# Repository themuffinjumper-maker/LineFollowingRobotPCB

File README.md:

# lfr_pcb

## Getting started

To make it easy for you to get started with GitLab, here's a list of recommended next steps.

Already a pro? Just edit this README.md and make it your own. Want to make it easy? [Use the template at the bottom](#editing-this-readme)!

## Add your files

- [ ] [Create](https://docs.gitlab.com/ee/user/project/repository/web_editor.html#create-a-file) or [upload](https://docs.gitlab.com/ee/user/project/repository/web_editor.html#upload-a-file) files
- [ ] [Add files using the command line](https://docs.gitlab.com/topics/git/add_files/#add-files-to-a-git-repository) or push an existing Git repository with the following command:

```
cd existing_repo
git remote add origin https://eng-git.canterbury.ac.nz/ogl15/lfr_pcb.git
git branch -M main
git push -uf origin main
```

## Integrate with your tools

- [ ] [Set up project integrations](https://eng-git.canterbury.ac.nz/ogl15/lfr_pcb/-/settings/integrations)

## Collaborate with your team

- [ ] [Invite team members and collaborators](https://docs.gitlab.com/ee/user/project/members/)
- [ ] [Create a new merge request](https://docs.gitlab.com/ee/user/project/merge_requests/creating_merge_requests.html)
- [ ] [Automatically close issues from merge requests](https://docs.gitlab.com/ee/user/project/issues/managing_issues.html#closing-issues-automatically)
- [ ] [Enable merge request approvals](https://docs.gitlab.com/ee/user/project/merge_requests/approvals/)
- [ ] [Set auto-merge](https://docs.gitlab.com/user/project/merge_requests/auto_merge/)

## Test and Deploy

Use the built-in continuous integration in GitLab.

- [ ] [Get started with GitLab CI/CD](https://docs.gitlab.com/ee/ci/quick_start/)
- [ ] [Analyze your code for known vulnerabilities with Static Application Security Testing (SAST)](https://docs.gitlab.com/ee/user/application_security/sast/)
- [ ] [Deploy to Kubernetes, Amazon EC2, or Amazon ECS using Auto Deploy](https://docs.gitlab.com/ee/topics/autodevops/requirements.html)
- [ ] [Use pull-based deployments for improved Kubernetes management](https://docs.gitlab.com/ee/user/clusters/agent/)
- [ ] [Set up protected environments](https://docs.gitlab.com/ee/ci/environments/protected_environments.html)

***

# Editing this README

When you're ready to make this README your own, just edit this file and use the handy template below (or feel free to structure it however you want - this is just a starting point!). Thanks to [makeareadme.com](https://www.makeareadme.com/) for this template.

## Suggestions for a good README

Every project is different, so consider which of these sections apply to yours. The sections used in the template are suggestions for most open source projects. Also keep in mind that while a README can be too long and detailed, too long is better than too short. If you think your README is too long, consider utilizing another form of documentation rather than cutting out information.

## Name
Choose a self-explaining name for your project.

## Description
Let people know what your project can do specifically. Provide context and add a link to any reference visitors might be unfamiliar with. A list of Features or a Background subsection can also be added here. If there are alternatives to your project, this is a good place to list differentiating factors.

## Badges
On some READMEs, you may see small images that convey metadata, such as whether or not all the tests are passing for the project. You can use Shields to add some to your README. Many services also have instructions for adding a badge.

## Visuals
Depending on what you are making, it can be a good idea to include screenshots or even a video (you'll frequently see GIFs rather than actual videos). Tools like ttygif can help, but check out Asciinema for a more sophisticated method.

## Installation
Within a particular ecosystem, there may be a common way of installing things, such as using Yarn, NuGet, or Homebrew. However, consider the possibility that whoever is reading your README is a novice and would like more guidance. Listing specific steps helps remove ambiguity and gets people to using your project as quickly as possible. If it only runs in a specific context like a particular programming language version or operating system or has dependencies that have to be installed manually, also add a Requirements subsection.

## Usage
Use examples liberally, and show the expected output if you can. It's helpful to have inline the smallest example of usage that you can demonstrate, while providing links to more sophisticated examples if they are too long to reasonably include in the README.

## Support
Tell people where they can go to for help. It can be any combination of an issue tracker, a chat room, an email address, etc.

## Roadmap
If you have ideas for releases in the future, it is a good idea to list them in the README.

## Contributing
State if you are open to contributions and what your requirements are for accepting them.

For people who want to make changes to your project, it's helpful to have some documentation on how to get started. Perhaps there is a script that they should run or some environment variables that they need to set. Make these steps explicit. These instructions could also be useful to your future self.

You can also document commands to lint the code or run tests. These steps help to ensure high code quality and reduce the likelihood that the changes inadvertently break something. Having instructions for running tests is especially helpful if it requires external setup, such as starting a Selenium server for testing in a browser.

## Authors and acknowledgment
Show your appreciation to those who have contributed to the project.

## License
For open source projects, say how it is licensed.

## Project status
If you have run out of energy or time for your project, put a note at the top of the README saying that development has slowed down or stopped completely. Someone may choose to fork your project or volunteer to step in as a maintainer or owner, allowing your project to keep going. You can also make an explicit request for maintainers.

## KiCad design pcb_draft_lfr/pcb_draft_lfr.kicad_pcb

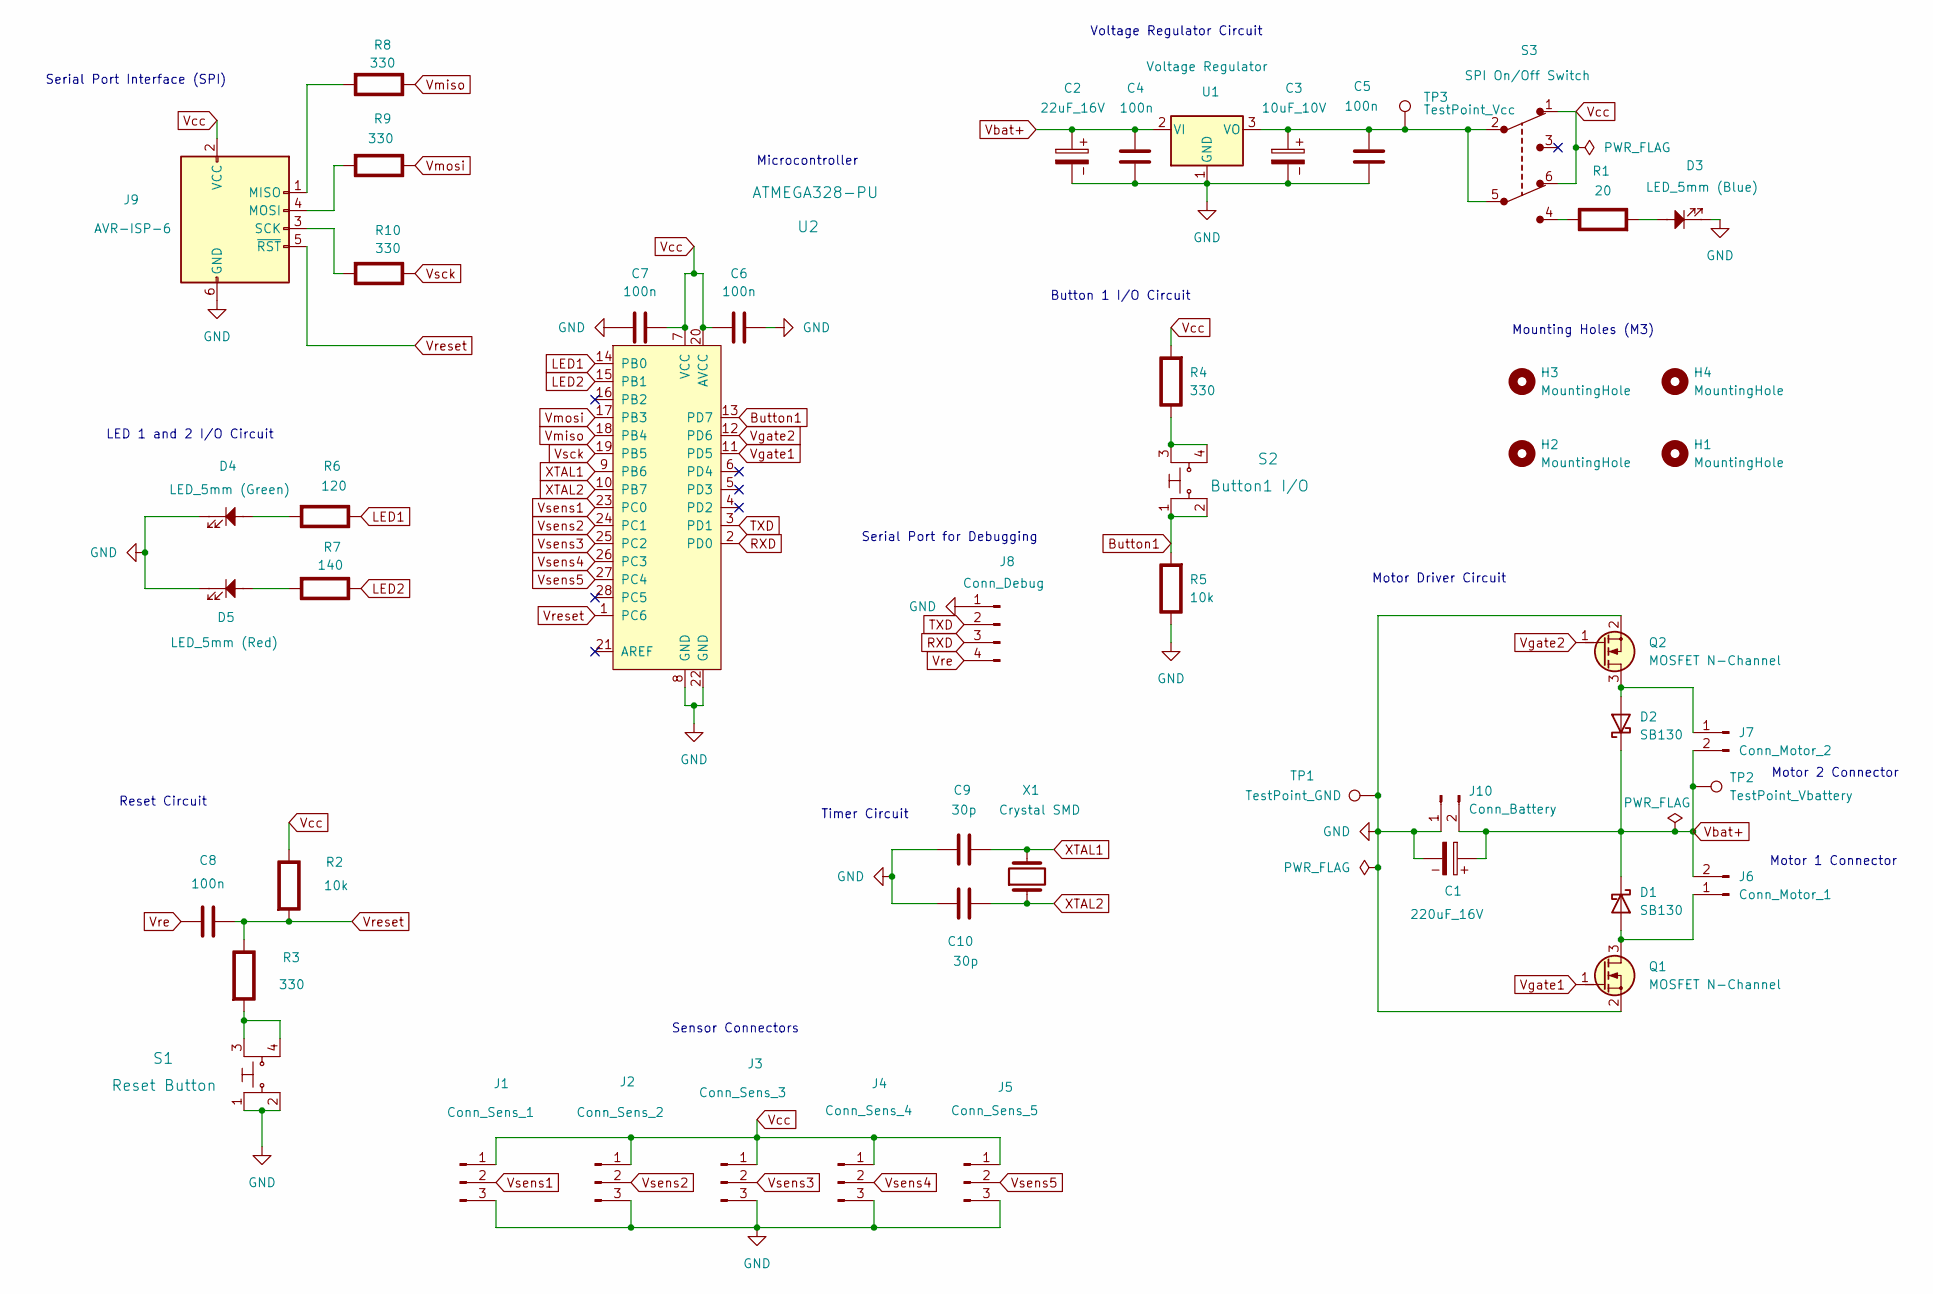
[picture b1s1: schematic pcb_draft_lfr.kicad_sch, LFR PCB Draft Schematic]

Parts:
C1: 220uF_16V; CP_Radial_D6.3mm_P2.50mm
C2: 22uF_16V; CP_Radial_D5.0mm_P2.00mm
C3: 10uF_10V; CP_Radial_D5.0mm_P2.00mm
C4, C5, C6, C7, C8: 100n; C_1206_3216Metric_Pad1.33x1.80mm_HandSolder
C9, C10: 30p; C_1206_3216Metric_Pad1.33x1.80mm_HandSolder
D1, D2: SB130; D_DO-41_SOD81_P10.16mm_Horizontal
D3: LED_5mm (Blue); LED_D5.0mm
D4: LED_5mm (Green); LED_D5.0mm
D5: LED_5mm (Red); LED_D5.0mm
H1, H2, H3, H4: MountingHole; MountingHole_3.2mm_M3
J1: Conn_Sens_1; PinHeader_1x03_P2.54mm_Vertical
J2: Conn_Sens_2; PinHeader_1x03_P2.54mm_Vertical
J3: Conn_Sens_3; PinHeader_1x03_P2.54mm_Vertical
J4: Conn_Sens_4; PinHeader_1x03_P2.54mm_Vertical
J5: Conn_Sens_5; PinHeader_1x03_P2.54mm_Vertical
J6: Conn_Motor_1; PinHeader_1x02_P2.54mm_Vertical
J7: Conn_Motor_2; PinHeader_1x02_P2.54mm_Vertical
J8: Conn_Debug; PinHeader_1x04_P2.54mm_Vertical
J9: AVR-ISP-6; IDC-Header_2x03_P2.54mm_Vertical
J10: Conn_Battery; PinHeader_1x02_P2.54mm_Vertical
Q1, Q2: MOSFET N-Channel; SC-59
R1: 20; R_0805_2012Metric_Pad1.20x1.40mm_HandSolder; Rating W
R2, R5: 10k; R_Axial_DIN0309_L9.0mm_D3.2mm_P12.70mm_Horizontal; Rating W
R3, R4, R8, R9, R10: 330; R_0805_2012Metric_Pad1.20x1.40mm_HandSolder; Rating W
R6: 120; R_0805_2012Metric_Pad1.20x1.40mm_HandSolder; Rating W
R7: 140; R_0805_2012Metric_Pad1.20x1.40mm_HandSolder; Rating W
S1: Reset Button; Switch_Tactile_THT_6x6mm_MJTP1230; MPN MJTP1230; Digi-Key_PN 679-2428-ND
S2: Button1 I/O; Switch_Tactile_THT_6x6mm_MJTP1230; MPN MJTP1230; Digi-Key_PN 679-2428-ND
S3: SPI On/Off Switch; SWITCH_011CQN; MPN JS202011SCQN; Digi-Key_PN 401-2002-1-ND
TP1: TestPoint_GND; TestPoint_Pad_D2.0mm
TP2: TestPoint_Vbattery; TestPoint_Pad_D2.0mm
TP3: TestPoint_Vcc; TestPoint_Pad_D2.0mm
U1: Voltage Regulator; TO-92_Inline
U2: ATMEGA328-PU; DIP-28_W7.62mm; MPN ATMEGA328-PU; Digi-Key_PN ATMEGA328-PU-ND
X1: Crystal SMD; Crystal_SMD_HC49-SD

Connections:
Button1: R5.2 (-), S2.1, S2.2, U2.13 (PD7)
GND: C1.2, C2.2, C3.2, C4.2, C5.2, C6.2, C7.1, C9.1, C10.1, D3.1, D4.1, D5.1, J1.3, J2.3, J3.3, J4.3, J5.3, J8.1, J9.6 (GND), J10.1, Q1.2 (S), Q2.2 (S), R5.1 (+), S1.1, S1.2, TP1.1, U1.1 (GND), U2.8 (GND), U2.22 (GND)
LED1: R6.1 (+), U2.14 (PB0)
LED2: R7.1 (+), U2.15 (PB1)
unnamed: D1.2 (A), J6.1, Q1.3 (D)
unnamed: D2.2 (A), J7.1, Q2.3 (D)
unnamed: J9.1 (MISO), R8.2 (-)
unnamed: J9.4 (MOSI), R9.2 (-)
unnamed: J9.3 (SCK), R10.2 (-)
unnamed: R1.1 (+), S3.4
unnamed: D3.2, R1.2 (-)
unnamed: R3.2 (-), S1.3, S1.4
unnamed: R4.1 (+), S2.3, S2.4
unnamed: D4.2, R6.2 (-)
unnamed: D5.2, R7.2 (-)
unnamed: C3.1, C5.1, S3.2, S3.5, TP3.1, U1.3 (VO)
RXD: J8.3, U2.2 (PD0)
TXD: J8.2, U2.3 (PD1)
Vbat+: C1.1, C2.1, C4.1, D1.1 (K), D2.1 (K), J6.2, J7.2, J10.2, TP2.1, U1.2 (VI)
Vcc: C6.1, C7.2, J1.1, J2.1, J3.1, J4.1, J5.1, J9.2 (VCC), R2.1 (+), R4.2 (-), S3.1, S3.6, U2.7 (VCC), U2.20 (AVCC)
Vgate1: Q1.1 (G), U2.11 (PD5)
Vgate2: Q2.1 (G), U2.12 (PD6)
Vmiso: R8.1 (+), U2.18 (PB4)
Vmosi: R9.1 (+), U2.17 (PB3)
Vre: C8.1, J8.4
Vreset: C8.2, J9.5 (~RST), R2.2 (-), R3.1 (+), U2.1 (PC6)
Vsck: R10.1 (+), U2.19 (PB5)
Vsens1: J1.2, U2.23 (PC0)
Vsens2: J2.2, U2.24 (PC1)
Vsens3: J3.2, U2.25 (PC2)
Vsens4: J4.2, U2.26 (PC3)
Vsens5: J5.2, U2.27 (PC4)
XTAL1: C9.2, U2.9 (PB6), X1.2
XTAL2: C10.2, U2.10 (PB7), X1.1

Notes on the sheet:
Motor Driver Circuit
Reset Circuit
Timer Circuit
Sensor Connectors
Button 1 I/O Circuit
LED 1 and 2 I/O Circuit
Voltage Regulator Circuit
Mounting Holes (M3)
Microcontroller
Serial Port Interface (SPI)
Motor 2 Connector
Motor 1 Connector
Serial Port for Debugging

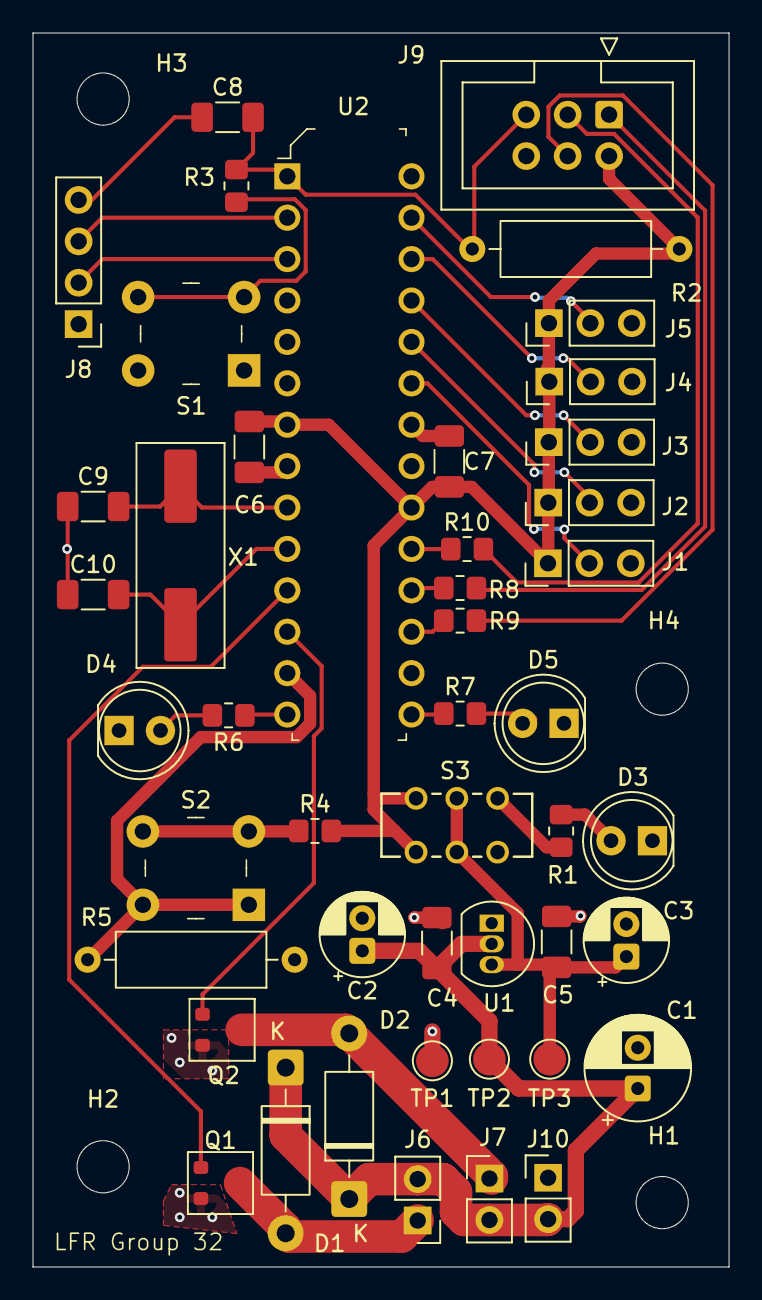
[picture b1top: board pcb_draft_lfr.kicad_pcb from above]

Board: 2 copper layers, 42.7 x 75.7 mm, 50 parts (0 on the bottom side), 34 nets.

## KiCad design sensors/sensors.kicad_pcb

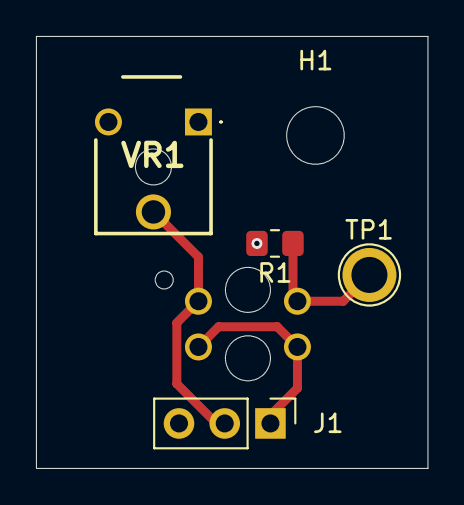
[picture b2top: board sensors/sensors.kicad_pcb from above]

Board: 2 copper layers, 21.8 x 24.0 mm, 6 parts (1 on the bottom side), 4 nets.

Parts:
H1: MountingHole; MountingHole_3.2mm_M3
J1: Conn 1x3; PinHeader_1x03_P2.54mm_Vertical
R1: 2k2; R_0805_2012Metric_Pad1.20x1.40mm_HandSolder
TP1: Cathode; TestPoint_Plated_Hole_D2.0mm
U1: TCRT5000; OPTO_TCRT5000
VR1: N6L50T0C-102-3030; N6L50T0C1033030

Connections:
GND: J1.3, R1.2, VR1.3 (CW)
unnamed: R1.1, TP1.1, U1.4
Vcc: J1.1, U1.1 (C), U1.3 (A)
Vout: J1.2, U1.2 (E), VR1.2 (WIPER)

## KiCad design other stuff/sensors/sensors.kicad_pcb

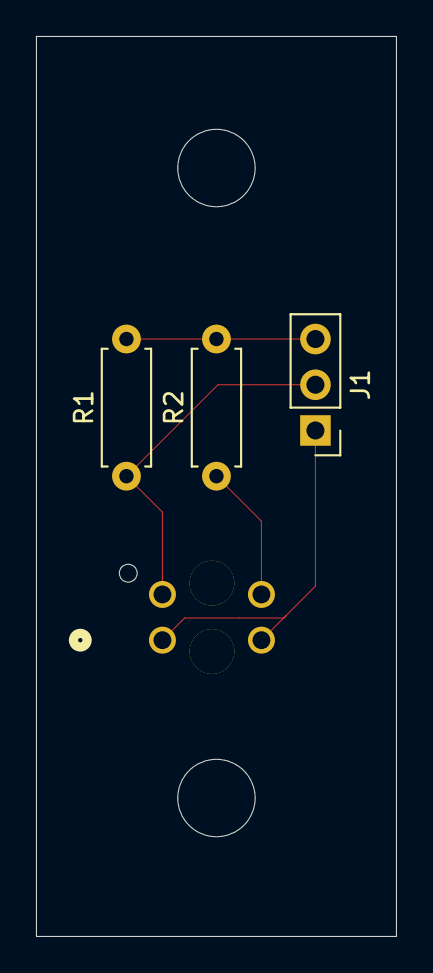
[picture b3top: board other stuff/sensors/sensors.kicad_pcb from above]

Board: 2 copper layers, 20.0 x 50.0 mm, 6 parts (1 on the bottom side), 4 nets.

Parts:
H1, H2: MountingHole; MountingHole_4.3mm_M4
J1: Conn_01x03_Pin; PinHeader_1x03_P2.54mm_Vertical
R1, R2: R; R_Axial_DIN0207_L6.3mm_D2.5mm_P7.62mm_Horizontal
U1: TCRT5000; TCRT5000_VIS

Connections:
GND: J1.3, R1.2, R2.2
unnamed: R2.1, U1.4
Vout: J1.2, R1.1, U1.2 (E)
Vss: J1.1, U1.1 (C), U1.3 (A)

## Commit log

2025-09-15 Readded files
2025-09-15 Submitted for reveiw
2025-09-18 REV3/4
2025-09-18 REV4
2025-09-18 Added files from 'Curtis', and updated 'sensors'
2025-09-18 Changed the layout of the files
2025-09-18 Added a potentiometer to the sensor board.
2025-09-18 Fixed the switch, and added more vias to ground for the mosfets.
2025-09-19 handin
2025-09-24 final handin
2025-09-25 Removed merge conflict message
2025-09-25 Created .step files for each component
2025-09-25 Started creating parts in SolidWorks
    Imported the model for the previous sensor design.
2025-09-26 3d model parts
2025-10-01 Upload New File
2025-10-04 Created the first Arduino files.
2025-10-09 3d printed parts
2025-10-09 Worked more on the sensor and motor controllers
2025-10-12 Fixed an issue which prevented the motors from running.
2025-10-13 changed the state machine
2025-10-13 Code thus far
2025-10-14 altered PID code
